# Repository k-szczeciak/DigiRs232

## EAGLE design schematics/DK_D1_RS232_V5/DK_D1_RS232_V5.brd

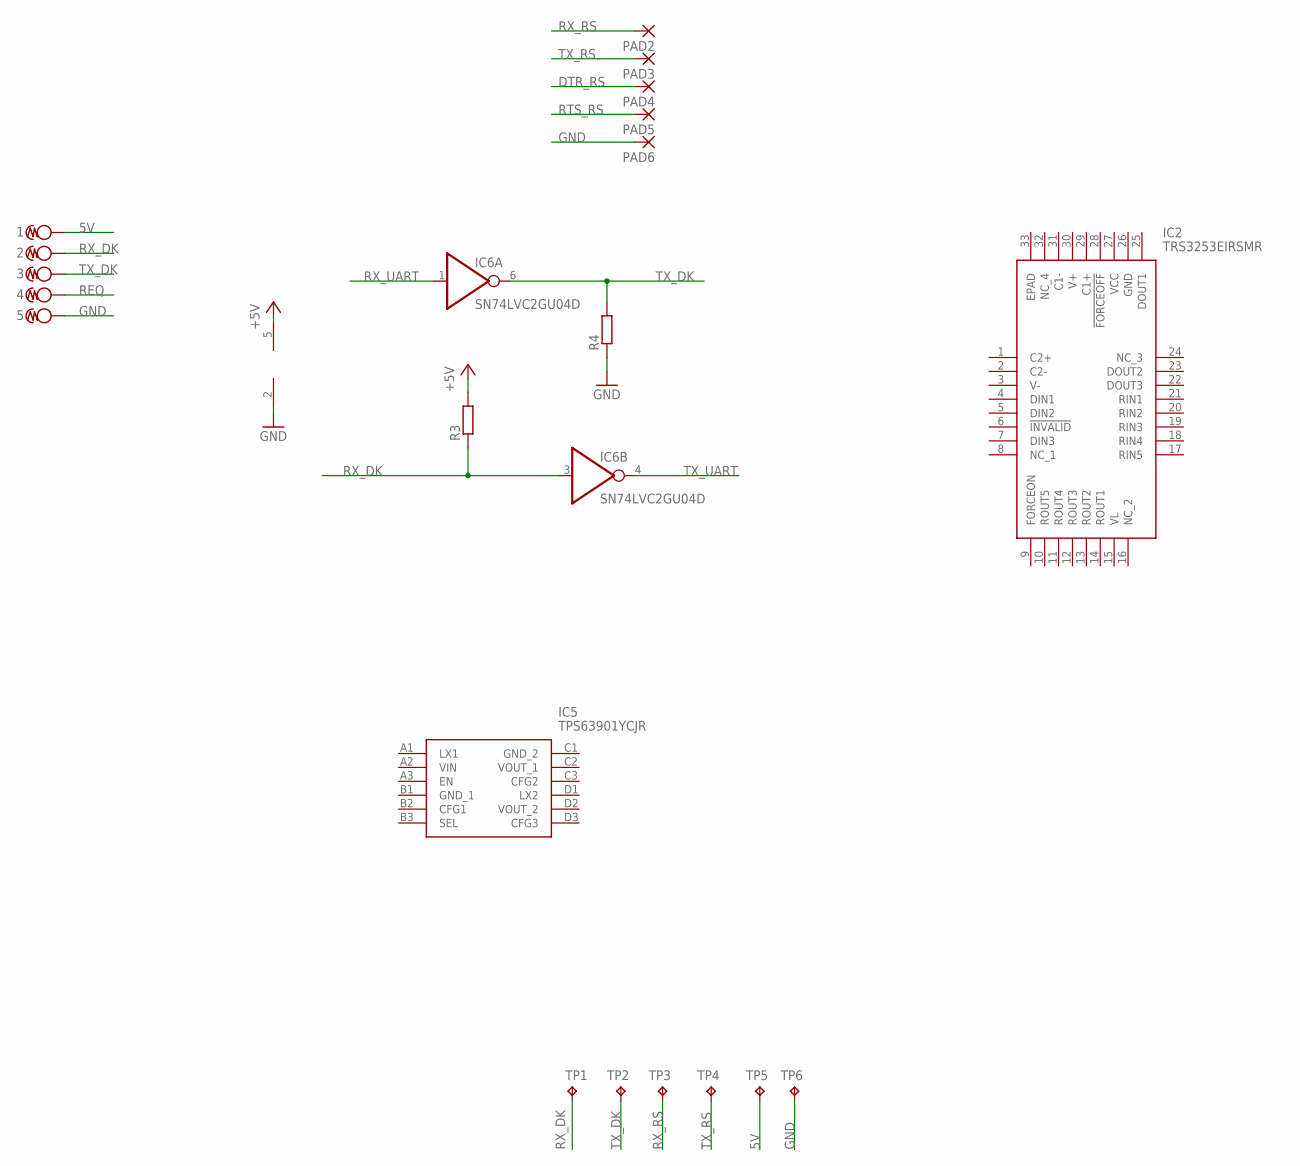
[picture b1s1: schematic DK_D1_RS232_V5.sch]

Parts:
1, 2, 3, 4, 5: 0975-0-15-20-80-14-11-0
IC2: TRS3253EIRSMR; QFN40P400X400X100-33N
IC5: TPS63901YCJR; BGA12C35P3X4_111X146X35
IC6: SN74LVC2GU04D; DBV6
PAD2, PAD3, PAD4, PAD5, PAD6: 1,6/0,8
R3, R4: R-EU_R0603; R0603
TP1, TP2, TP3, TP4, TP5, TP6: TPB1,27; B1,27

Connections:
5V: 1.P$1, TP5.TP
+5V: IC6.5 (5V), R3.2
DTR_RS: PAD4.1
GND: 5.P$1, IC6.2 (GND), PAD6.1, R4.1, TP6.TP
REQ: 4.P$1
RTS_RS: PAD5.1
RX_DK: 2.P$1, IC6.3 (A), R3.1, TP1.TP
RX_RS: PAD2.1, TP3.TP
RX_UART: IC6.1 (A)
TX_DK: 3.P$1, IC6.6 (Y), R4.2, TP2.TP
TX_RS: PAD3.1, TP4.TP
TX_UART: IC6.4 (Y)

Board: 2 copper layers, 21 parts (0 on the bottom side), 7 nets, no tracks yet.

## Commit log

2023-10-08 docs update
2023-10-10 todo update
